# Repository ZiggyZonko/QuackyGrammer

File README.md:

# QuackyGrammer ~ The portable, Type C PIC Programmer

Recently, I rediscovered a collection of PIC Microcontrollers and was fascinated on how they work, programming them, and the simplicity of a REAL microcontroller. Before this, I was learning assembly through a previous project of mine, LindlesOS, so these microcontrollers were a great way of demonstrating the practicality of Assembly. I picked up a k150 from AliExpress, only to realise the drivers are impossible to find, setup and are mind-numbing to install...

This is what brought me to my project, I was wondering, how could I improve the programming of PIC Microcontrollers while making it portable, and simplistic. I stumbled upon the PICKIT 2 and learnt about the difference between ZIF and ISCP sockets, learning that ISCP was wayyy more accessible, and may be suitable for my project. After countless hours of planning, wondering, and researching I agreed on things to include in my project

- USB Type C Connector ~ Usually on programmers they use USB Type B because of it's constant power rather than being wired to power.
  
- PIC18F2550 ~ The heart and brains of the project. The K150 uses PIC16F628A but I wanted to add further programming capabilities and not include excess chips, like on the K150.
  
- Connector ~ The defining factor of the PICKIT 2 is the ability to plug about 5 wires into the microcontroller, and upload your code from a PICKIT application, which is exactly what I can replicate with this project, for even more accessibility.

Which brings me to my project, QuackyGrammer ✨

The QuackyGrammer is a USB Type C powered, portable, ISCP connecting PIC Programmer, powered by the mighty PIC18F2550. The Programmer is aimed to make PIC Programming easy with a flawless, PICKIT 2 inspired connecting system, and a very portable USB Type C connection port. The duck theme is inspired by a new nickname I recently acquired, Quackery, and as you can tell by my other projects, I stick with this theme now.

The Bill of Materials is in BOM.csv

The firmware for this project, is uploading the PK2V023200.hex into the PIC18F2550 with the PICKITV2 programmer software.

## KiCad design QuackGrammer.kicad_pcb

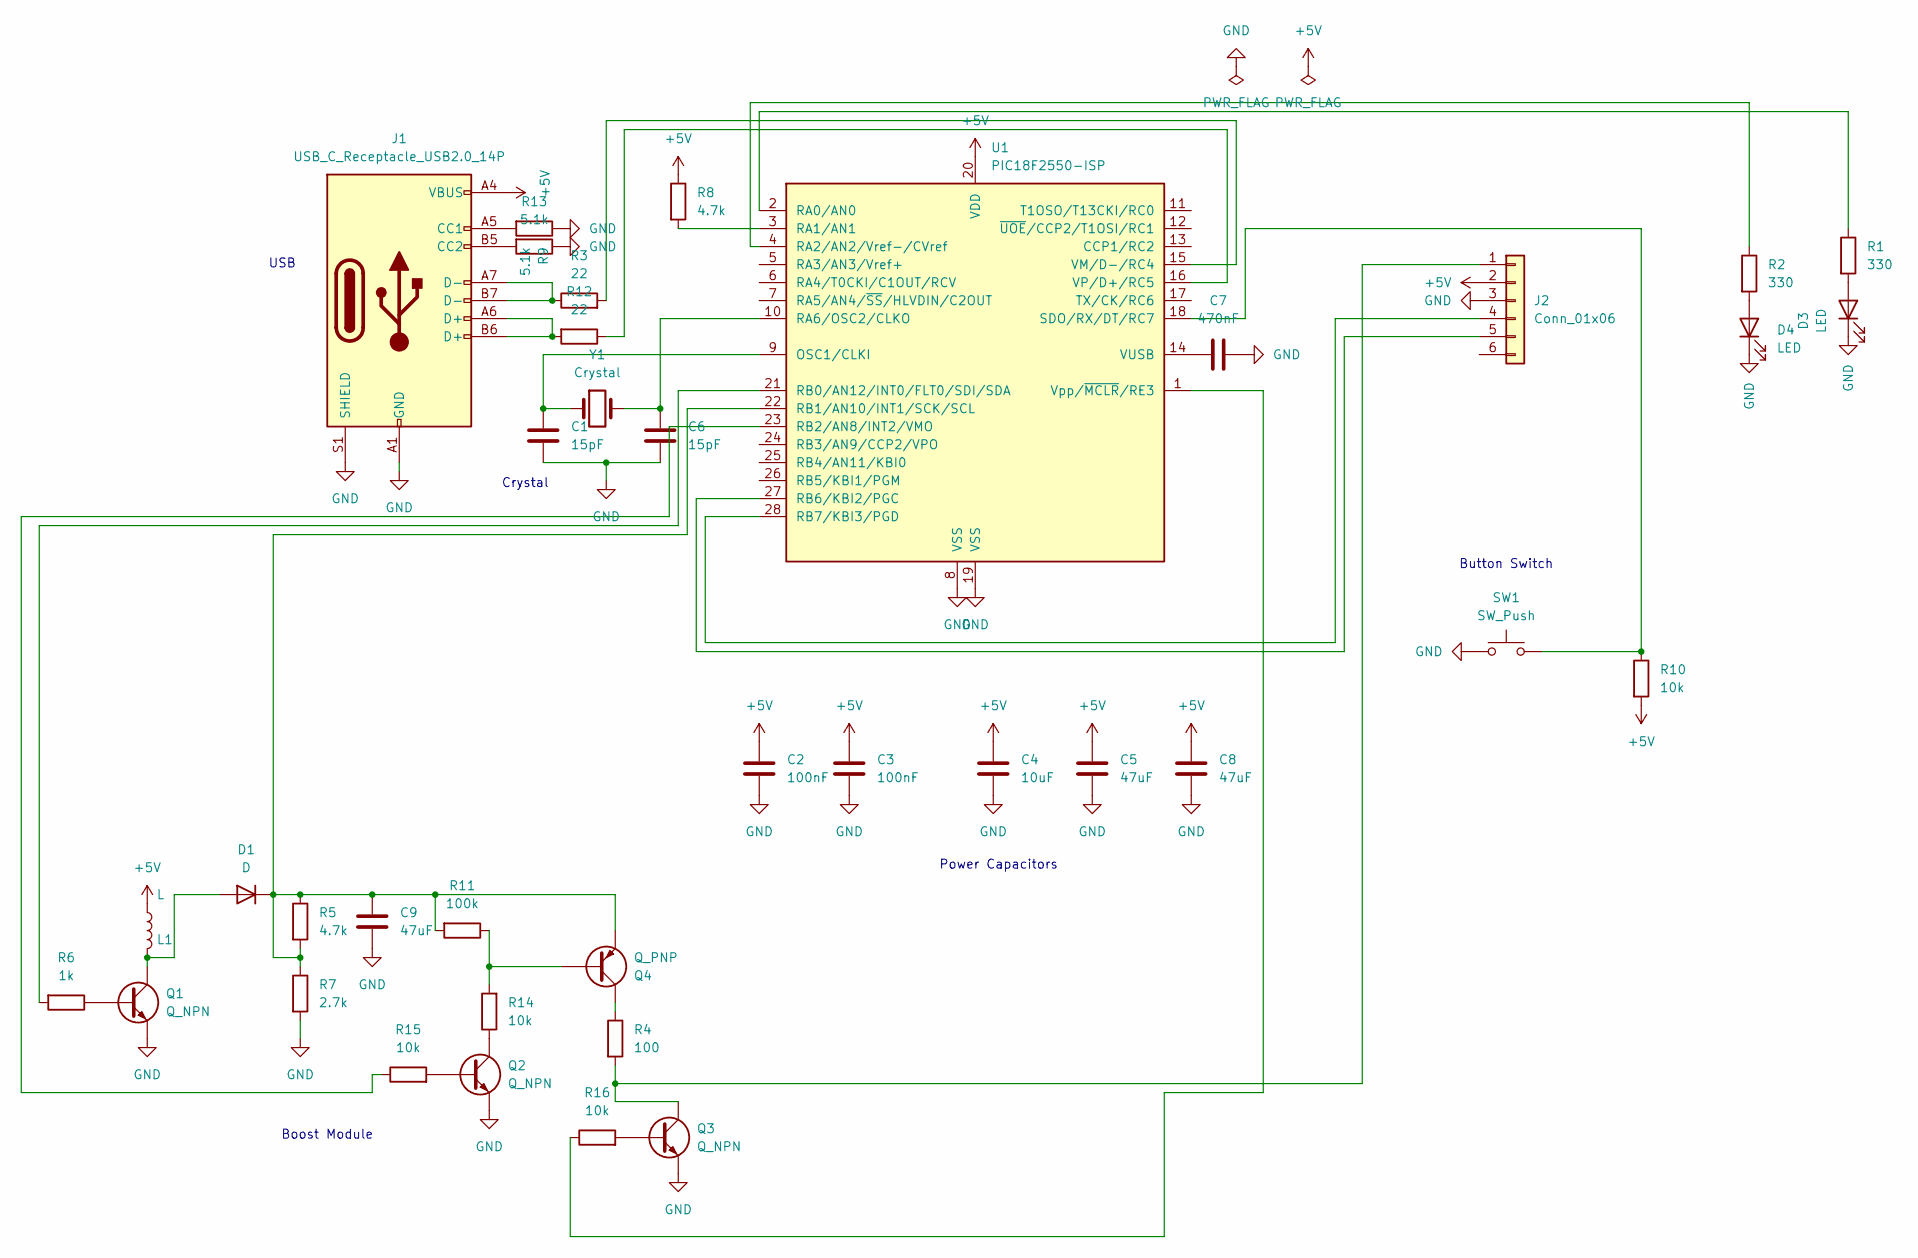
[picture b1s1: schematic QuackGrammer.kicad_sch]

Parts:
C1, C6: 15pF; C_Disc_D5.0mm_W2.5mm_P5.00mm
C2, C3: 100nF; C_Disc_D5.0mm_W2.5mm_P5.00mm
C4: 10uF; CP_Radial_D5.0mm_P2.50mm
C5, C8, C9: 47uF; CP_Radial_D5.0mm_P2.50mm
C7: 470nF; C_Disc_D5.0mm_W2.5mm_P5.00mm
D1: D; D_DO-35_SOD27_P7.62mm_Horizontal
D3, D4: LED; LED_D3.0mm
J1: USB_C_Receptacle_USB2.0_14P; USB_C_Receptacle_GCT_USB4105-xx-A_16P_TopMnt_Horizontal
J2: Conn_01x06; PinHeader_1x06_P2.54mm_Horizontal
L1: L; R_Axial_DIN0207_L6.3mm_D2.5mm_P7.62mm_Horizontal
Q1, Q2, Q3: Q_NPN; TO-92_Inline
Q4: Q_PNP; TO-92_Inline
R1, R2: 330; R_Axial_DIN0207_L6.3mm_D2.5mm_P7.62mm_Horizontal
R3, R12: 22; R_Axial_DIN0207_L6.3mm_D2.5mm_P7.62mm_Horizontal
R4: 100; R_Axial_DIN0207_L6.3mm_D2.5mm_P7.62mm_Horizontal
R5, R8: 4.7k; R_Axial_DIN0207_L6.3mm_D2.5mm_P7.62mm_Horizontal
R6: 1k; R_Axial_DIN0207_L6.3mm_D2.5mm_P7.62mm_Horizontal
R7: 2.7k; R_Axial_DIN0207_L6.3mm_D2.5mm_P7.62mm_Horizontal
R9, R13: 5.1k; R_Axial_DIN0207_L6.3mm_D2.5mm_P7.62mm_Horizontal
R10, R14, R15, R16: 10k; R_Axial_DIN0207_L6.3mm_D2.5mm_P7.62mm_Horizontal
R11: 100k; R_Axial_DIN0207_L6.3mm_D2.5mm_P7.62mm_Horizontal
SW1: SW_Push; SW_PUSH_6mm
U1: PIC18F2550-ISP; DIP-28_W7.62mm
Y1: Crystal; Crystal_HC49-U_Vertical

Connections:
+5V: C2.1, C3.1, C4.1, C5.1, C8.1, J1.A4 (VBUS), J1.A9 (VBUS), J1.B4 (VBUS), J1.B9 (VBUS), J2.2, L1.2, R8.1, R10.2, U1.20 (VDD)
GND: C1.2, C2.2, C3.2, C4.2, C5.2, C6.2, C7.1, C8.2, C9.2, D3.1 (K), D4.1 (K), J1.A1 (GND), J1.A12 (GND), J1.B1 (GND), J1.B12 (GND), J1.S1 (SHIELD), J2.3, Q1.3 (E), Q2.3 (E), Q3.3 (E), R7.2, R9.1, R13.1, SW1.1, U1.8 (VSS), U1.19 (VSS)
unnamed: D1.2 (A), L1.1, Q1.1 (C)
unnamed: C9.1, D1.1 (K), Q4.3 (E), R5.1, R5.2, R7.1, R11.2, U1.22 (RB1/AN10/INT1/SCK/SCL)
unnamed: D3.2 (A), R1.2
unnamed: D4.2 (A), R2.2
unnamed: J1.A5 (CC1), R9.2
unnamed: J1.B5 (CC2), R13.2
unnamed: J1.A6 (D+), J1.B6 (D+), R12.2
unnamed: J1.A7 (D-), J1.B7 (D-), R3.1
unnamed: J2.1, Q3.1 (C), R4.2
unnamed: J2.4, U1.28 (RB7/KBI3/PGD)
unnamed: J2.5, U1.27 (RB6/KBI2/PGC)
unnamed: Q1.2 (B), R6.1
unnamed: Q2.2 (B), R15.2
unnamed: Q2.1 (C), R14.1
unnamed: Q3.2 (B), R16.2
unnamed: Q4.2 (B), R11.1, R14.2
unnamed: Q4.1 (C), R4.1
unnamed: C1.1, U1.9 (OSC1/CLKI), Y1.1
unnamed: R1.1, U1.2 (RA0/AN0)
unnamed: R8.2, U1.3 (RA1/AN1)
unnamed: R2.1, U1.4 (RA2/AN2/Vref-/CVref)
unnamed: C6.1, U1.10 (RA6/OSC2/CLKO), Y1.2
unnamed: R6.2, U1.21 (RB0/AN12/INT0/FLT0/SDI/SDA)
unnamed: R15.1, U1.23 (RB2/AN8/INT2/VMO)
unnamed: R10.1, SW1.2, U1.18 (SDO/RX/DT/RC7)
unnamed: R3.2, U1.15 (VM/D-/RC4)
unnamed: R12.1, U1.16 (VP/D+/RC5)
unnamed: C7.2, U1.14 (VUSB)
unnamed: R16.1, U1.1 (Vpp/~MCLR/RE3)

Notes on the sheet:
Boost Module
Power Capacitors
Button Switch
Crystal
USB

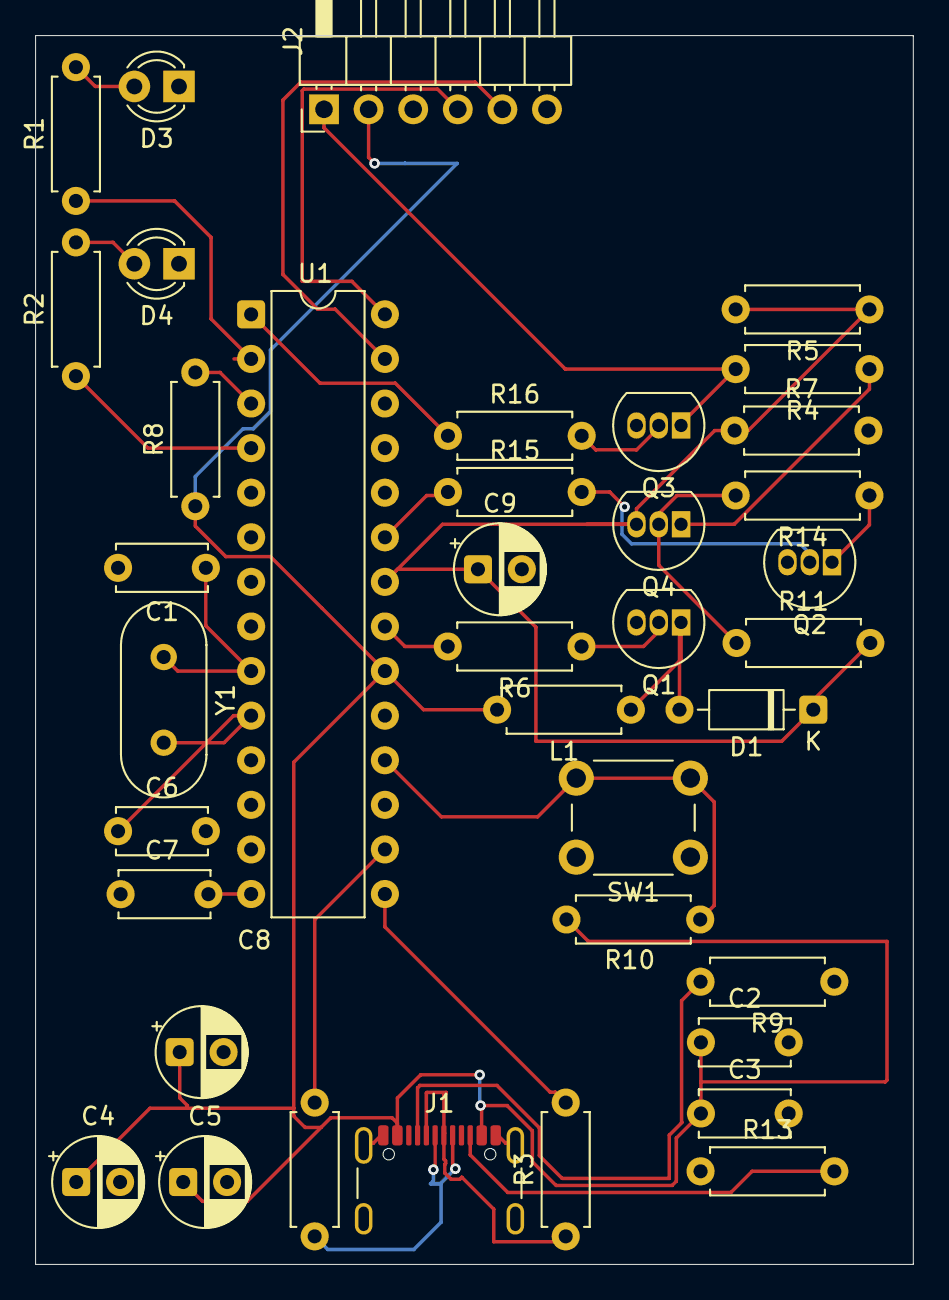
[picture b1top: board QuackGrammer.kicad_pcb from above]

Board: 2 copper layers, 50.0 x 70.0 mm, 38 parts (0 on the bottom side), 31 nets.

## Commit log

2026-04-08 BOM created
2026-04-14 Create Hello
2026-04-14 Rename QuackGrammer.kicad_pcb to Model/QuackGrammer.kicad_pcb
2026-04-14 Rename QuackGrammer.kicad_pro to Model/QuackGrammer.kicad_pro
2026-04-14 Rename QuackGrammer.kicad_sch to Model/QuackGrammer.kicad_sch
2026-04-14 Rename QuackGrammer.step to Model/QuackGrammer.step
2026-04-14 Rename BOM.csv to PartList.csv
2026-04-14 Rename QuackyGrammer-bom (1).csv to QuackyGrammer-bom.csv
